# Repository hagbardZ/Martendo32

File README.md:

assets/65467d34-9345-4316-92dd-8e191f508759" />
Kicad files for Martendo32.
An ESP32-P4 based Retro Game console

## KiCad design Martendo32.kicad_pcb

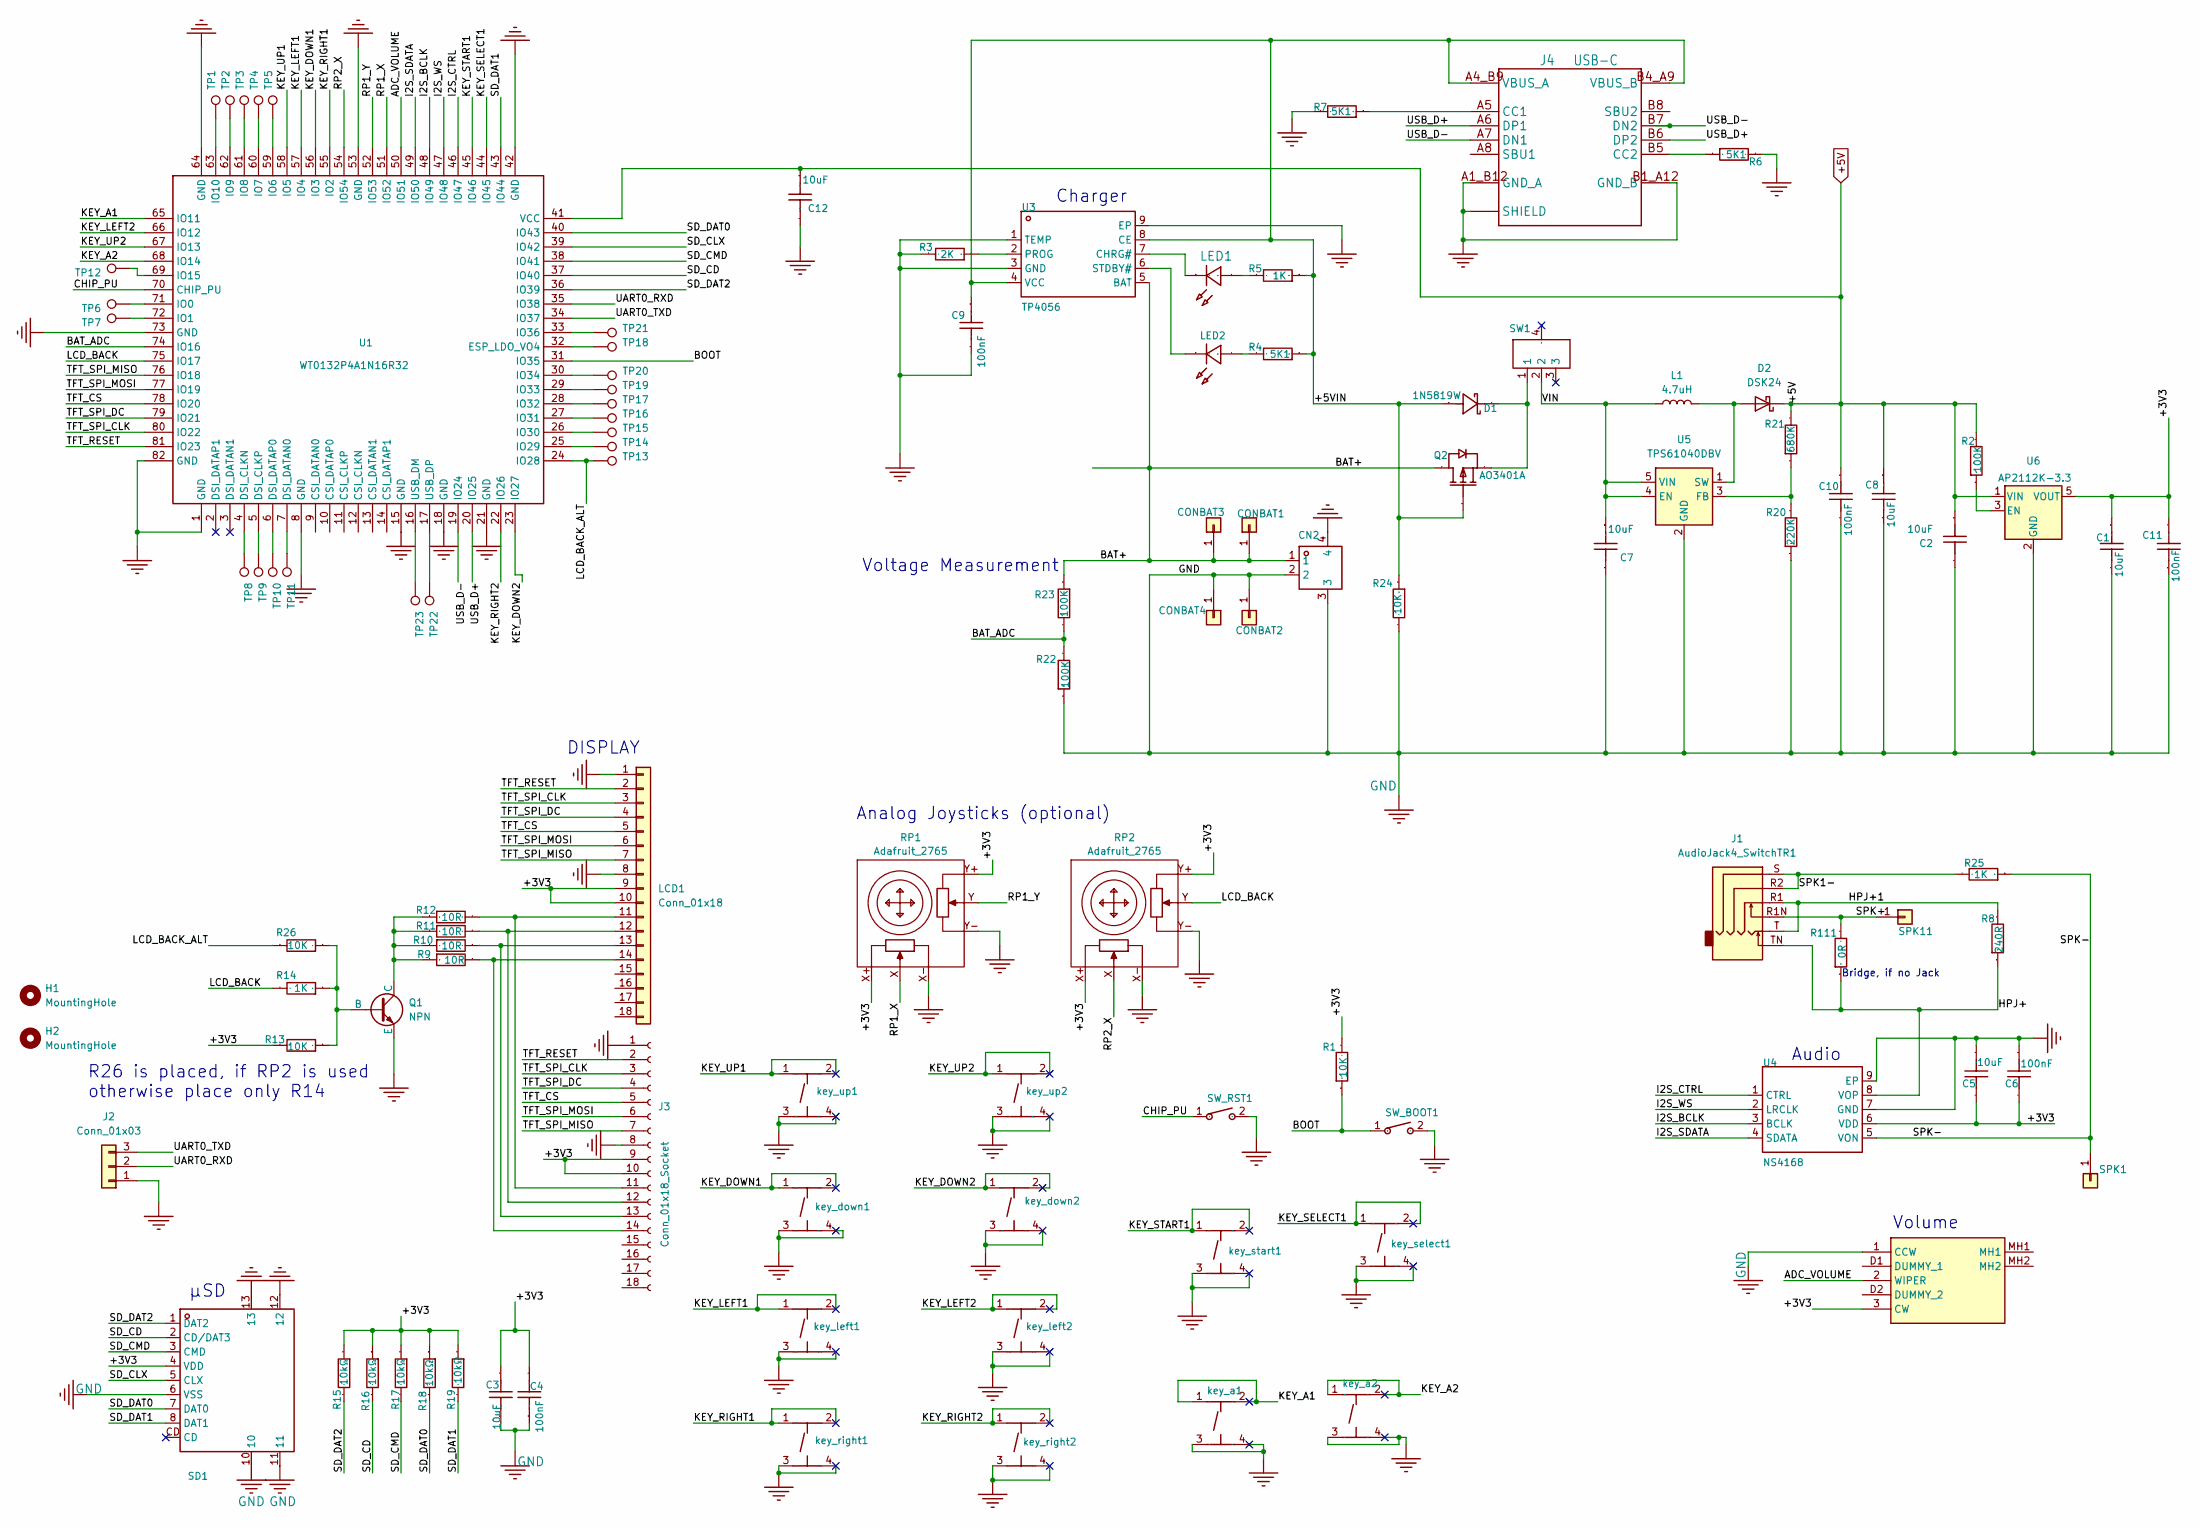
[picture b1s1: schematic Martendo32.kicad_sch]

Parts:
C1, C2, C5: 10uF; 0603; Manufacturer Part CL10A106MA8NRNC; LCSC Part Name 10uF ±20% 25V
C3: 10uF; 0603; Manufacturer Part CGA0603X5R106K100JT; LCSC Part Name 10uF ±10% 10V
C4: 100nF; 0603; Manufacturer Part CGA0603X7R104K500JT; LCSC Part Name 100nF ±10% 50V
C6, C11: 100nF; 0603; Manufacturer Part CL10A106MA8NRNC; LCSC Part Name 10uF ±20% 25V
C7, C8: 10uF; 0603
C9, C10: 100nF; 0603
C12: 10uF; 0805
CN2: ZX-MX1.25-2PWT; CONN-SMD_2P-P1.25_D125F2W1-2W2P43; Manufacturer Part ZX-MX1.25-2PWT; LCSC Part Name 1x2P 间距:1.25mm 卧贴
CONBAT1, CONBAT2: Conn_01x01; PinHeader_1x01_P2.54mm_Vertical
CONBAT3, CONBAT4: Conn_01x01; TestPoint_Pad_3.0x3.0mm
D1: 1N5819W; SOD-123_L2.7-W1.6-LS3.7-RDaaa; Manufacturer Part 1N5819W; LCSC Part Name 电压:40V 电流:350mA
D2: DSK24; SOD-123FL_L2.7-W1.8-LS3.8-RD
H1, H2: MountingHole; MountingHole_5mm
J1: AudioJack4_SwitchTR1; AUDIO-SMD_HOOYA_PJ-242a
J2: Conn_01x03; PinSocket_1x03_P2.54mm_Vertical
J3: Conn_01x18_Socket; 687118183722
J4: USB-C; AMPHENOL_GSB1C41110SSHR
L1: 4.7uH; IND-SMD_L2.5-W2.0_MHCH252012A
LCD1: Conn_01x18; ILI9341-2.8a
LED1: LED0603-RD_GREEN
LED2: LED0603-RD_RED
Q1: NPN; SOT-23-3_L2.9-W1.6-P1.90-LS2.8-BRaaa
Q2: AO3401A; SOT-23-3_L2.9-W1.6-P1.90-LS2.8-BR; Manufacturer Part AO3401A; LCSC Part Name P沟道 耐压:30V 电流:4A
R1, R13, R24: 10K; 0603
R2, R22, R23: 100K; 0603
R3: 2K; 0603
R4, R6, R7: 5K1; 0603
R5, R14, R25: 1K; 0603
R8: 240R; 0603
R9, R10, R11, R12: 10R; 0603
R15, R16, R17, R18, R19: 10kΩ; 0603; Voltage-Supply(Max) 75V; Manufacturer Part 0603WAF1002T5E; LCSC Part Name 厚膜电阻 10kΩ ±1% 100mW
R20: 220K; 0603
R21: 680K; 0603
R26: 10K; R_0603_1608Metric_Pad0.98x0.95mm_HandSolder
R111: 0R; 0603
RP1, RP2: Adafruit_2765; PartNumber 2765
SD1: TF-SMD_TF-01A; Manufacturer Part TF PUSH; LCSC Part Name 自弹式 MicroSD卡(TF卡) 卡座
SPK1, SPK11: Conn_01x01; TestPoint_Pad_D2.5mm
SW1: SK-3296S-01-L3; SW-SMD_MSK12C02-HB; Manufacturer Part SK-3296S-01-L3; LCSC Part Name 柄长2.5mm 卧贴双档 滑动开关
SW_BOOT1: 3*4 龟仔/微动/轻触开关; SW-SMD_L3.9-W3.0-P4.45; Manufacturer Part 3*4 龟仔/微动/轻触开关; LCSC Part Name 3*4 龟仔/微动/轻触开关
SW_RST1: 3*4 龟仔/微动/轻触开关; SW-SMD_L3.9-W3.0-P4.45; Manufacturer Part 3*4 龟仔/微动/轻触开关; LCSC Part Name 3*4 龟仔/微动/轻触开关
TP1, TP2, TP3, TP4, TP5, TP6, TP7, TP8, TP9, TP10, TP11, TP12, TP13, TP14, TP15, TP16, TP17, TP18, TP19, TP20, TP21, TP22, TP23: TestPoint; TestPoint_Pad_D1.0mm
U1: WT0132P4A1N16R32; COMM-SMD_L25.0-W20.0-P1.00_WT0132P4-A1
U3: TP4056; ESOP-8_L4.9-W3.9-P1.27-LS6.0-BL-EP; Manufacturer Part TP4056; LCSC Part Name TP4056
U4: NS4168; ESOP-8_L4.9-W3.9-P1.27-LS6.0-BL-EP; Manufacturer Part NS4168; LCSC Part Name NS4168
U5: TPS61040DBV; SOT-23-5_L3.0-W1.7-P0.95-LS2.8-BR
U6: AP2112K-3.3; SOT-23-5_L2.9-W1.6-P0.95-LS2.8-BR
VR1: RK10J11E002Y; Manufacturer_Part_Number RK10J11E002Y; Mouser Part Number 688-RK10J11E002Y
key_a1: TS-1187A-B-A-B; 430451031836; Manufacturer Part TS-1187A-B-A-B; LCSC Part Name 5.1*5.1*1.5mm 立贴 轻触开关
key_a2: TS-1187A-B-A-B; DTSM-6; Manufacturer Part TS-1187A-B-A-B; LCSC Part Name 5.1*5.1*1.5mm 立贴 轻触开关
key_down1, key_down2: TS-1187A-B-A-B; 430451031836; Manufacturer Part TS-1187A-B-A-B; LCSC Part Name 5.1*5.1*1.5mm 立贴 轻触开关
key_left1, key_left2: TS-1187A-B-A-B; 430451031836; Manufacturer Part TS-1187A-B-A-B; LCSC Part Name 5.1*5.1*1.5mm 立贴 轻触开关
key_right1, key_right2: TS-1187A-B-A-B; 430451031836; Manufacturer Part TS-1187A-B-A-B; LCSC Part Name 5.1*5.1*1.5mm 立贴 轻触开关
key_select1: TS-1187A-B-A-B; 430451031836; Manufacturer Part TS-1187A-B-A-B; LCSC Part Name 5.1*5.1*1.5mm 立贴 轻触开关
key_start1: TS-1187A-B-A-B; 430451031836; Manufacturer Part TS-1187A-B-A-B; LCSC Part Name 5.1*5.1*1.5mm 立贴 轻触开关
key_up1, key_up2: TS-1187A-B-A-B; 430451031836; Manufacturer Part TS-1187A-B-A-B; LCSC Part Name 5.1*5.1*1.5mm 立贴 轻触开关

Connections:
+5V: C2.1, C8.1, C10.1, C12.1, D2.1 (K), R2.2, R21.2, U1.41 (VCC), U6.1 (VIN)
/+3V3: C1.1, C3.2, C4.2, C5.2, C6.2, C11.2, J3.9, J3.10, LCD1.9, LCD1.10, R1.2, R13.2, R15.1, R16.1, R17.1, R18.1, R19.1, RP1.X+, RP1.Y+, RP2.X+, RP2.Y+, SD1.4 (VDD), U4.6 (VDD), U6.5 (VOUT), VR1.3 (CW)
/+5VIN: C9.1, D1.1 (A), J4.A4_B9 (VBUS_A), J4.B4_A9 (VBUS_B), Q2.1 (G), R4.1, R5.1, R24.1, U3.4 (VCC), U3.8 (CE)
/ADC_VOLUME: U1.50 (IO51), VR1.2 (WIPER)
/BAT+: CN2.1, CONBAT1.1 (Pin_1_1), CONBAT3.1 (Pin_1_1), Q2.3 (D), R23.1, U3.5 (BAT)
/BAT_ADC: R22.2, R23.2, U1.74 (IO16)
/BOOT: R1.1, SW_BOOT1.1, U1.31 (IO35)
/CHIP_PU: SW_RST1.1, U1.70 (CHIP_PU)
/HPJ+: J1.TN, R8.1, R111.1, U4.8 (VOP)
/HPJ+1: J1.R1, J1.T, R8.2
/I2S_BCLK: U1.48 (IO49), U4.3 (BCLK)
/I2S_CTRL: U1.46 (IO47), U4.1 (CTRL)
/I2S_SDATA: U1.49 (IO50), U4.4 (SDATA)
/I2S_WS: U1.47 (IO48), U4.2 (LRCLK)
/KEY_A1: U1.65 (IO11), key_a1.1 (A), key_a1.2 (B)
/KEY_A2: U1.68 (IO14), key_a2.1 (A), key_a2.2 (B)
/KEY_DOWN1: U1.56 (IO3), key_down1.1 (A), key_down1.2 (B)
/KEY_DOWN2: U1.23 (IO27), key_down2.1 (A), key_down2.2 (B)
/KEY_LEFT1: U1.57 (IO4), key_left1.1 (A), key_left1.2 (B)
/KEY_LEFT2: U1.66 (IO12), key_left2.1 (A), key_left2.2 (B)
/KEY_RIGHT1: U1.55 (IO2), key_right1.1 (A), key_right1.2 (B)
/KEY_RIGHT2: U1.22 (IO26), key_right2.1 (A), key_right2.2 (B)
/KEY_SELECT1: U1.44 (IO45), key_select1.1 (A), key_select1.2 (B)
/KEY_START1: U1.45 (IO46), key_start1.1 (A), key_start1.2 (B)
/KEY_UP1: U1.58 (IO5), key_up1.1 (A), key_up1.2 (B)
/KEY_UP2: U1.67 (IO13), key_up2.1 (A), key_up2.2 (B)
/LCD_BACK: R14.2, RP2.Y, U1.75 (IO17)
/LCD_BACK_ALT: R26.2, TP13.1 (1_1), U1.24 (IO28)
/RP1_X: RP1.X, U1.51 (IO52)
/RP1_Y: RP1.Y, U1.52 (IO53)
/RP2_X: RP2.X, U1.54 (IO54)
/SD_CD: R16.2, SD1.2 (CD/DAT3), U1.37 (IO40)
/SD_CLX: SD1.5 (CLX), U1.39 (IO42)
/SD_CMD: R17.2, SD1.3 (CMD), U1.38 (IO41)
/SD_DAT0: R18.2, SD1.7 (DAT0), U1.40 (IO43)
/SD_DAT1: R19.2, SD1.8 (DAT1), U1.43 (IO44)
/SD_DAT2: R15.2, SD1.1 (DAT2), U1.36 (IO39)
/SPK1-: J1.R2, J1.S, R25.2
/SPK+: J1.R1N, R111.2, SPK11.1 (Pin_1_1)
/SPK-: R25.1, SPK1.1 (Pin_1_1), U4.5 (VON)
/TFT_CS: J3.5, LCD1.5, U1.78 (IO20)
/TFT_RESET: J3.2, LCD1.2, U1.81 (IO23)
/TFT_SPI_CLK: J3.3, LCD1.3, U1.80 (IO22)
/TFT_SPI_DC: J3.4, LCD1.4, U1.79 (IO21)
/TFT_SPI_MISO: J3.7, LCD1.7, U1.76 (IO18)
/TFT_SPI_MOSI: J3.6, LCD1.6, U1.77 (IO19)
/UART0_RXD: J2.2, U1.35 (IO38)
/UART0_TXD: J2.3, U1.34 (IO37)
/USB_D+: J4.A6 (DP1), J4.B6 (DP2), U1.20 (IO25)
/USB_D-: J4.A7 (DN1), J4.B7 (DN2), U1.19 (IO24)
/VIN: C7.1, L1.1, SW1.2, U5.4 (EN), U5.5 (VIN)
GND: C1.2, C2.2, C3.1, C4.1, C5.1, C6.1, C7.2, C8.2, C9.2, C10.2, C11.1, C12.2, CN2.2, CN2.3, CN2.4, CONBAT2.1 (Pin_1_1), CONBAT4.1 (Pin_1_1), J2.1, J3.1, J3.8, J3.Z1, J3.Z2, J4.A1_B12 (GND_A), J4.B1_A12 (GND_B), J4.SH1 (SHIELD), J4.SH2 (SHIELD), J4.SH3 (SHIELD), J4.SH4 (SHIELD), LCD1.1, LCD1.8, Q1.3 (E), R3.2, R6.2, R7.2, R20.1, R22.1, R24.2, RP1.X-, RP1.Y-, RP2.X-, RP2.Y-, SD1.6 (VSS), SD1.10, SD1.11, SD1.12, SD1.13, SW_BOOT1.2, SW_RST1.2, U1.1 (GND), U1.8 (GND), U1.15 (GND), U1.18 (GND), U1.21 (GND), U1.42 (GND), U1.53 (GND), U1.64 (GND), U1.73 (GND), U1.82 (GND), U3.1 (TEMP), U3.3 (GND), U3.9 (EP), U4.7 (GND), U4.9 (EP), U5.2 (GND), U6.2 (GND), VR1.1 (CCW), key_a1.3 (C), key_a1.4 (D), key_a2.3 (C), key_a2.4 (D), key_down1.3 (C), key_down1.4 (D), key_down2.3 (C), key_down2.4 (D), key_left1.3 (C), key_left1.4 (D), key_left2.3 (C), key_left2.4 (D), key_right1.3 (C), key_right1.4 (D), key_right2.3 (C), key_right2.4 (D), key_select1.3 (C), key_select1.4 (D), key_start1.3 (C), key_start1.4 (D), key_up1.3 (C), key_up1.4 (D), key_up2.3 (C), key_up2.4 (D); also elsewhere on the board
unnamed: D1.2 (C), Q2.2 (S), SW1.1
unnamed: D2.2 (A), L1.2, U5.1 (SW)
unnamed: J3.11, LCD1.11, R12.2
unnamed: J3.12, LCD1.12, R11.2
unnamed: J3.13, LCD1.13, R10.2
unnamed: J3.14, LCD1.14, R9.2
unnamed: J4.A5 (CC1), R7.1
unnamed: J4.B5 (CC2), R6.1
unnamed: LED1.2 (A), R5.2
unnamed: LED1.1 (C), U3.7 (CHRG#)
unnamed: LED2.2 (A), R4.2
unnamed: LED2.1 (C), U3.6 (STDBY#)
unnamed: Q1.2 (B), R13.1, R14.1, R26.1
unnamed: Q1.1 (C), R9.1, R10.1, R11.1, R12.1
unnamed: TP8.1 (1_1), U1.4 (DSI_CLKN)
unnamed: TP9.1 (1_1), U1.5 (DSI_CLKP)
unnamed: TP11.1 (1_1), U1.7 (DSI_DATAN0)
unnamed: TP10.1 (1_1), U1.6 (DSI_DATAP0)
unnamed: TP18.1 (1_1), U1.32 (ESP_LDO_VO4)
unnamed: TP6.1 (1_1), U1.71 (IO0)
unnamed: TP7.1 (1_1), U1.72 (IO1)
unnamed: TP5.1 (1_1), U1.59 (IO6)
unnamed: TP4.1 (1_1), U1.60 (IO7)
unnamed: TP3.1 (1_1), U1.61 (IO8)
unnamed: TP2.1 (1_1), U1.62 (IO9)
unnamed: TP1.1 (1_1), U1.63 (IO10)
unnamed: TP12.1 (1_1), U1.69 (IO15)
unnamed: TP14.1 (1_1), U1.25 (IO29)
unnamed: TP15.1 (1_1), U1.26 (IO30)
unnamed: TP16.1 (1_1), U1.27 (IO31)
unnamed: TP17.1 (1_1), U1.28 (IO32)
unnamed: TP19.1 (1_1), U1.29 (IO33)
unnamed: TP20.1 (1_1), U1.30 (IO34)
unnamed: TP21.1 (1_1), U1.33 (IO36)
unnamed: TP23.1 (1_1), U1.16 (USB_DM)
unnamed: TP22.1 (1_1), U1.17 (USB_DP)
unnamed: R3.1, U3.2 (PROG)
unnamed: R20.2, R21.1, U5.3 (FB)
unnamed: R2.1, U6.3 (EN)

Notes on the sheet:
R26 is placed, if RP2 is used otherwise place only R14
Analog Joysticks (optional)
µSD
DISPLAY
Audio
Volume
Charger
Voltage Measurement
Bridge, if no Jack

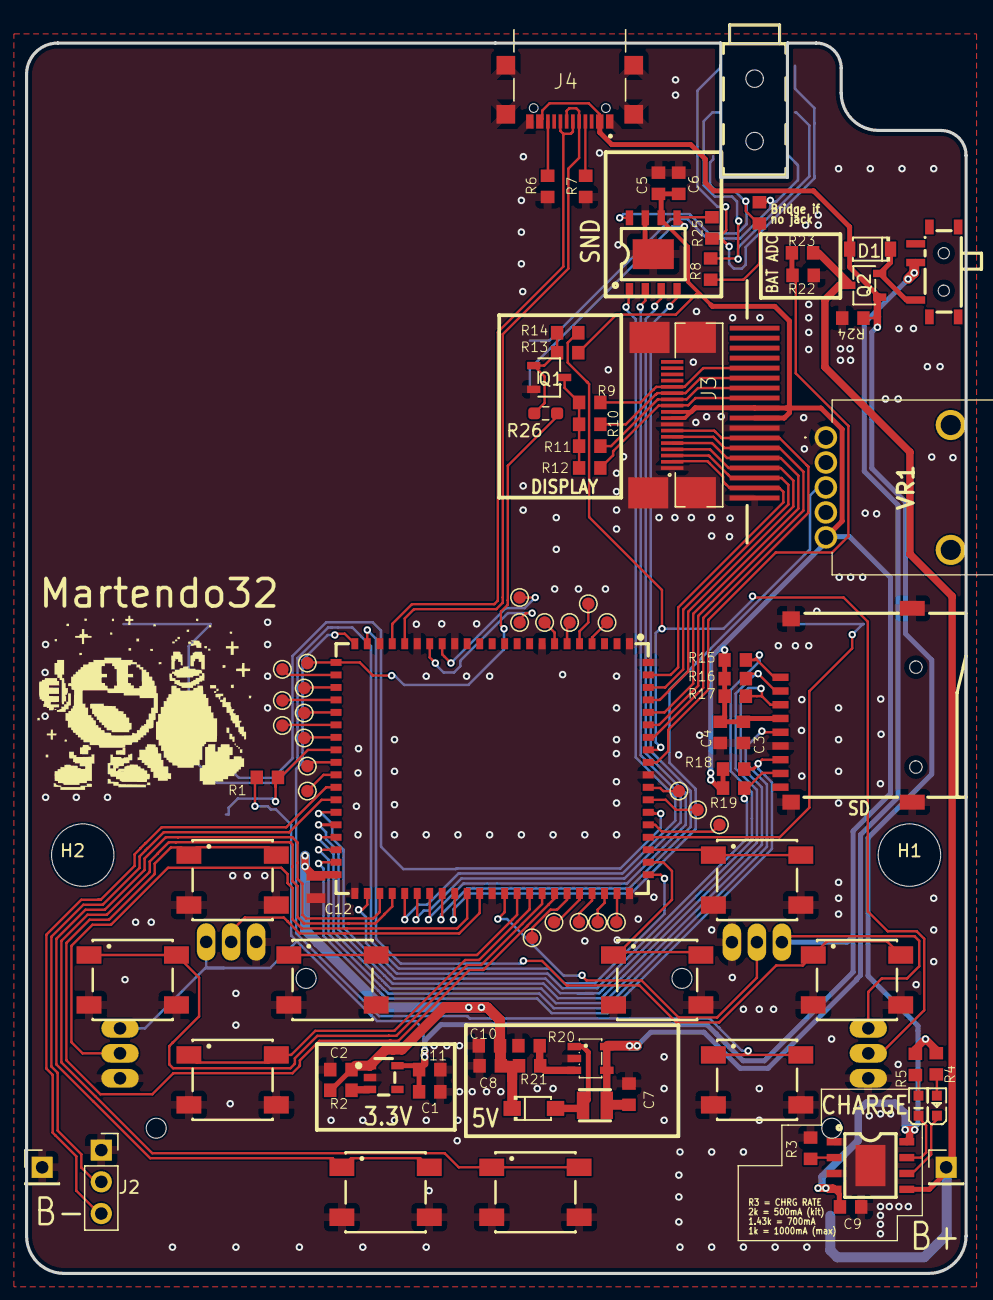
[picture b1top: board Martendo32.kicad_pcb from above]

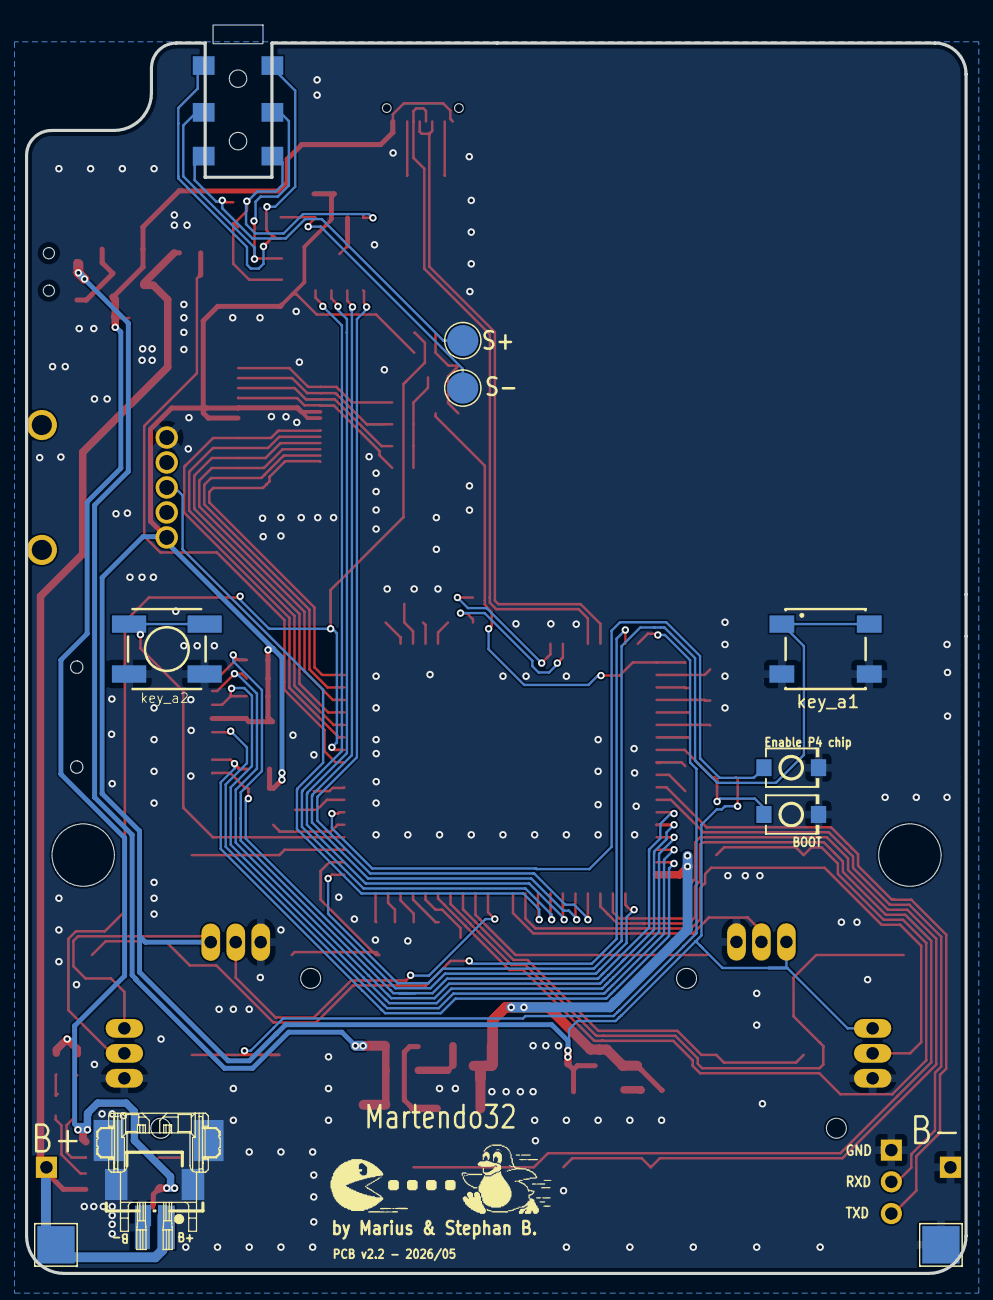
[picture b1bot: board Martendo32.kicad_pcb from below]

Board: 2 copper layers, 75.2 x 100.0 mm, 109 parts (9 on the bottom side), 91 nets.

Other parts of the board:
X22, X23: (no value)

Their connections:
GND: X22.Z2, X23.Z1; also elsewhere on the board

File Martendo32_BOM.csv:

"ID";"Bezeichner";"Footprint";"Stückzahl";"Bezeichnung";"Anbieter und Referenz";
1;"C1, C2, C3, C5, C7, C8";"0603";6;"10uF";;;
2;"C4, C6, C9, C10, C11";"0603";5;"100nF";;;
3;"C12";"0805";1;"10uF";;;
4;"CN2";"CONN-SMD_2P-P1.25_D125F2W1-2W2P43";1;"ZX-MX1.25-2PWT";;;
5;"CONBAT1, CONBAT2";"PinHeader_1x01_P2.54mm_Vertical";2;"Conn_01x01";;;
6;"CONBAT3, CONBAT4";"TestPoint_Pad_3.0x3.0mm";2;"Conn_01x01";;;
7;"D1";"SOD-123_L2.7-W1.6-LS3.7-RDaaa";1;"1N5819W";;;
8;"D2";"SOD-123FL_L2.7-W1.8-LS3.8-RD";1;"DSK24";;;
9;"J1";"AUDIO-SMD_HOOYA_PJ-242a";1;"AudioJack4_SwitchTR1";;;
10;"J2";"PinSocket_1x03_P2.54mm_Vertical";1;"Conn_01x03";;;
11;"J3";"687118183722";1;"Conn_01x18_Socket";;;
12;"J4";"AMPHENOL_GSB1C41110SSHR";1;"USB-C";;;
13;"key_a1, key_down1, key_down2, key_left1, key_left2, key_right1, key_right2, key_select1, key_start1, key_up1, key_up2";"430451031836";11;"TS-1187A-B-A-B";;;
14;"key_a2";"DTSM-6";1;"TS-1187A-B-A-B";;;
15;"L1";"IND-SMD_L2.5-W2.0_MHCH252012A";1;"4.7uH";;;
16;"LCD1";"ILI9341-2.8a";1;"Conn_01x18";;;
17;"LED1";"LED0603-RD_GREEN";1;"~";;;
18;"LED2";"LED0603-RD_RED";1;"~";;;
19;"Q1";"SOT-23-3_L2.9-W1.6-P1.90-LS2.8-BRaaa";1;"NPN";;;
20;"Q2";"SOT-23-3_L2.9-W1.6-P1.90-LS2.8-BR";1;"AO3401A";;;
21;"R1, R13";"0603";2;"10K";;;
22;"R2, R22, R23";"0603";3;"100K";;;
23;"R3";"0603";1;"2K";;;
24;"R4, R6, R7";"0603";3;"5K1";;;
25;"R5, R14, R25";"0603";3;"1K";;;
26;"R8";"0603";1;"240R";;;
27;"R9, R10, R11, R12";"0603";4;"10R";;;
28;"R15, R16, R17, R18, R19";"0603";5;"10kΩ";;;
29;"R20";"0603";1;"220K";;;
30;"R21";"0603";1;"680K";;;
31;"R24";"0603";1;"10K";;;
32;"R26";"R_0603_1608Metric_Pad0.98x0.95mm_HandSolder";1;"10K";;;
33;"R111";"0603";1;"0R";;;
34;"REF**";"BATT_CONN_SMT_292173";1;"BATT_CONN_SMT_292173";;;
35;"RP1, RP2";"Adafruit_2765";2;"Adafruit_2765";;;
36;"SD1";"TF-SMD_TF-01A";1;"~";;;
37;"SPK1, SPK11";"TestPoint_Pad_D2.5mm";2;"Conn_01x01";;;
38;"SW1";"SW-SMD_MSK12C02-HB";1;"SK-3296S-01-L3";;;
39;"SW_BOOT1, SW_RST1";"SW-SMD_L3.9-W3.0-P4.45";2;"3*4 龟仔/微动/轻触开关";;;
40;"TP1, TP2, TP3, TP4, TP5, TP6, TP7, TP8, TP9, TP10, TP11, TP12, TP13, TP14, TP15, TP16, TP17, TP18, TP19, TP20, TP21, TP22, TP23";"TestPoint_Pad_D1.0mm";23;"TestPoint";;;
41;"U1";"COMM-SMD_L25.0-W20.0-P1.00_WT0132P4-A1";1;"~";;;
42;"U3";"ESOP-8_L4.9-W3.9-P1.27-LS6.0-BL-EP";1;"TP4056";;;
43;"U4";"ESOP-8_L4.9-W3.9-P1.27-LS6.0-BL-EP";1;"NS4168";;;
44;"U5";"SOT-23-5_L3.0-W1.7-P0.95-LS2.8-BR";1;"TPS61040DBV";;;
45;"U6";"SOT-23-5_L2.9-W1.6-P0.95-LS2.8-BR";1;"AP2112K-3.3";;;
46;"VR1";"RK10J11E002Y";1;"RK10J11E002Y";;;
47;"X22, X23";"";2;"";;;

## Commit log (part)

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2026-01-22 Add files via upload
    added Analog Joysticks RP1/RP1
2026-01-22 Add files via upload
    improved Silkscreen
2026-04-28 Add files via upload
    Upper Housing with frame for IPS Display (IPS Display is smaller than TFT)
2026-04-28 Update README.md
    added picture from housing
2026-04-28 Add files via upload
    updated chamfers
2026-04-28 Add files via upload
    added stl parts
2026-04-28 Update README.md
    new image
2026-04-29 Add files via upload
    changed IPS frame
2026-05-28 added value to U1
